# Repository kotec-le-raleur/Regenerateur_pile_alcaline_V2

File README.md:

# Regenerateur_pile_alcaline_V2
Encore un autre projet à la con pour tenter de recharger des piles alcalines

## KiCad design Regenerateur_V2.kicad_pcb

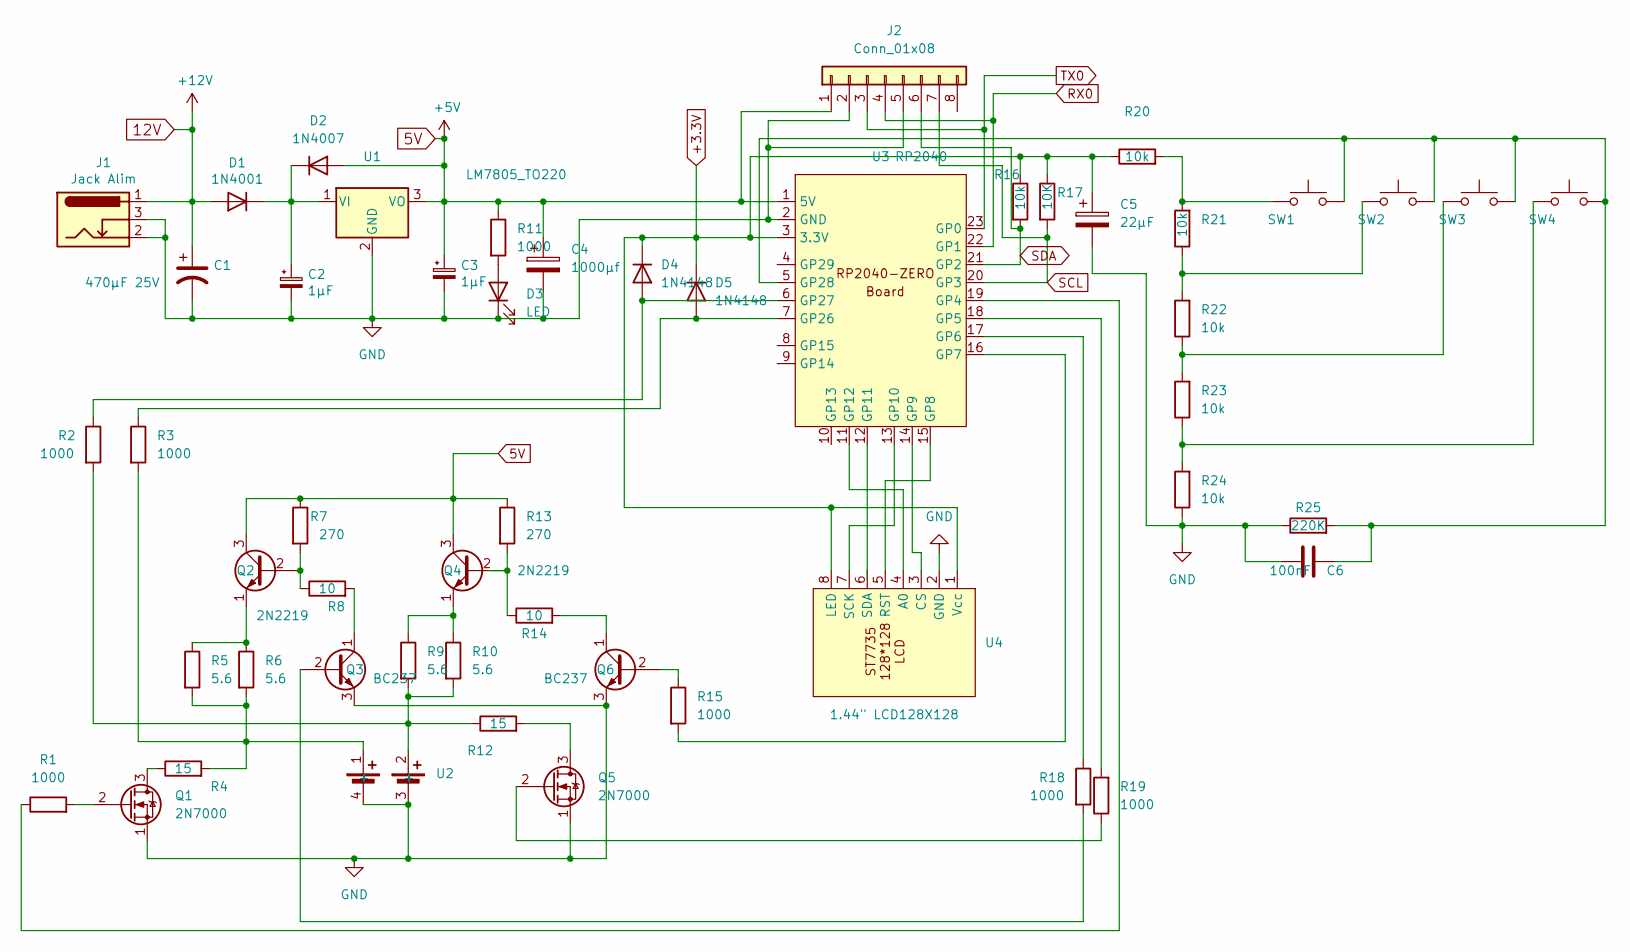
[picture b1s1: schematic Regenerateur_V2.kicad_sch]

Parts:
C1: 470µF 25V; CP_Radial_D10.0mm_P5.00mm
C2, C3: 1µF; C_1206_3216Metric_Pad1.33x1.80mm_HandSolder
C4: 1000µf; CP_Radial_D10.0mm_P7.50mm
C5: 22µF; CP_Radial_D5.0mm_P2.50mm
C6: 100nF; C_Rect_L7.0mm_W2.5mm_P5.00mm
D1: 1N4001; D_DO-41_SOD81_P10.16mm_Horizontal
D2: 1N4007; D_DO-41_SOD81_P10.16mm_Horizontal
D3: LED; LED_D5.0mm
D4, D5: 1N4148; D_A-405_P7.62mm_Horizontal
J1: Jack Alim; BarrelJack_Wuerth_6941xx301002
J2: Conn_01x08; PinHeader_1x08_P2.54mm_Vertical
Q1, Q5: 2N7000; TO-92_HandSolder
Q2, Q4: 2N2219; TO-5-4
Q3, Q6: BC237; TO-92_HandSolder
R1, R2, R3, R11, R15, R18, R19: 1000; R_Axial_DIN0204_L3.6mm_D1.6mm_P7.62mm_Horizontal
R4, R12: 15; R_Axial_DIN0204_L3.6mm_D1.6mm_P7.62mm_Horizontal
R5, R6, R9, R10: 5.6; R_Axial_DIN0204_L3.6mm_D1.6mm_P7.62mm_Horizontal
R7, R13: 270; R_Axial_DIN0204_L3.6mm_D1.6mm_P7.62mm_Horizontal
R8, R14: 10; R_Axial_DIN0204_L3.6mm_D1.6mm_P7.62mm_Horizontal
R16, R20, R21, R22, R23, R24: 10k; R_Axial_DIN0204_L3.6mm_D1.6mm_P7.62mm_Horizontal
R17: 10K; R_Axial_DIN0204_L3.6mm_D1.6mm_P7.62mm_Horizontal
R25: 220K; R_Axial_DIN0204_L3.6mm_D1.6mm_P7.62mm_Horizontal
SW1, SW2, SW3, SW4: SW_Push; SW_PUSH_6mm_H13mm
U1: LM7805_TO220; TO-220-3_Vertical
U2: AAX2_Case
U3: RP2040; RP2040_zero_mini
U4: 1.44" LCD128X128; LCD128X128

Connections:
5V: C3.1, C4.1, D2.2 (A), J2.1, Q2.3 (C), Q4.3 (C), R7.1, R11.1, R13.1, U1.3 (VO), U3.1 (5V)
12V: C1.1, D1.2 (A), J1.1
+3.3V: C5.1, D4.1 (K), D5.1 (K), R16.1, R17.1, R20.1, U3.3 (3.3V), U4.1 (Vcc), U4.8 (LED)
GND: C1.2, C2.2, C3.2, C4.2, C5.2, C6.1, D3.1 (K), J1.2, J1.3, J2.2, J2.5, Q1.1 (S), Q3.3 (E), Q5.1 (S), Q6.3 (E), R24.1, R25.1, U1.2 (GND), U2.3 (-), U2.4 (-), U3.2 (GND), U4.2 (GND)
unnamed: C2.1, D1.1 (K), D2.1 (K), U1.1 (VI)
unnamed: D3.2 (A), R11.2
unnamed: D4.2 (A), R2.1, U3.6 (GP27)
unnamed: D5.2 (A), R3.1, U3.7 (GP26)
unnamed: Q1.3 (D), R4.1
unnamed: Q1.2 (G), R1.2
unnamed: Q2.2 (B), Q2.4, R7.2, R8.1
unnamed: Q2.1 (E), R5.1, R6.1
unnamed: Q3.2 (B), R18.2
unnamed: Q3.1 (C), R8.2
unnamed: Q4.2 (B), Q4.4, R13.2, R14.1
unnamed: Q4.1 (E), R9.1, R10.1
unnamed: Q5.3 (D), R12.2
unnamed: Q5.2 (G), R19.1
unnamed: Q6.2 (B), R15.1
unnamed: Q6.1 (C), R14.2
unnamed: R3.2, R4.2, R5.2, R6.2, U2.1 (+)
unnamed: R2.2, R9.2, R10.2, R12.1, U2.2 (+)
unnamed: R20.2, R21.2, SW1.1
unnamed: R21.1, R22.2, SW2.1
unnamed: R22.1, R23.2, SW3.1
unnamed: R23.1, R24.2, SW4.1
unnamed: R1.1, U3.19 (GP4)
unnamed: R19.2, U3.18 (GP5)
unnamed: R18.1, U3.17 (GP6)
unnamed: R15.2, U3.16 (GP7)
unnamed: U3.15 (GP8), U4.5 (RST)
unnamed: U3.14 (GP9), U4.3 (CS)
unnamed: U3.13 (GP10), U4.7 (SCK)
unnamed: U3.11 (GP12), U4.4 (A0)
unnamed: C6.2, R25.2, SW1.2, SW2.2, SW3.2, SW4.2, U3.5 (GP28)
RX0: J2.4, U3.22 (GP1)
SCL: J2.7, R17.2, U3.20 (GP3)
SDA: J2.6, R16.2, U3.21 (GP2)
TX0: J2.3, U3.23 (GP0)

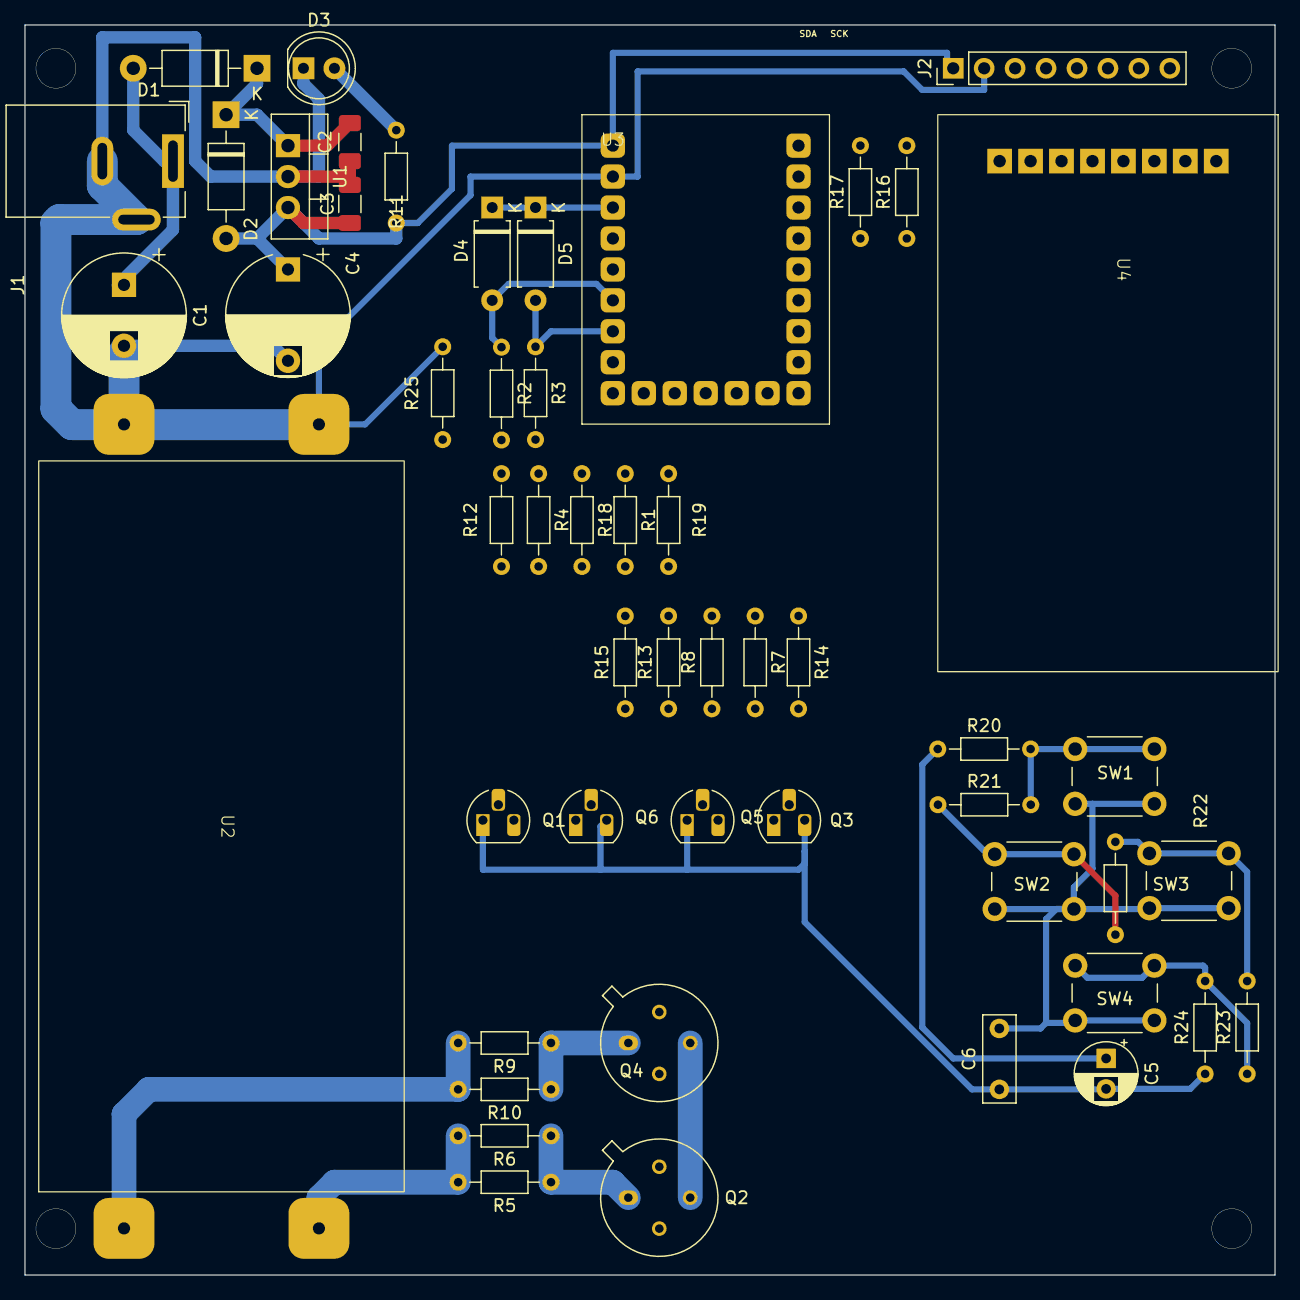
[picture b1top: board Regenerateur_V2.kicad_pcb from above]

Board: 2 copper layers, 102.6 x 102.6 mm, 52 parts (0 on the bottom side), 39 nets.

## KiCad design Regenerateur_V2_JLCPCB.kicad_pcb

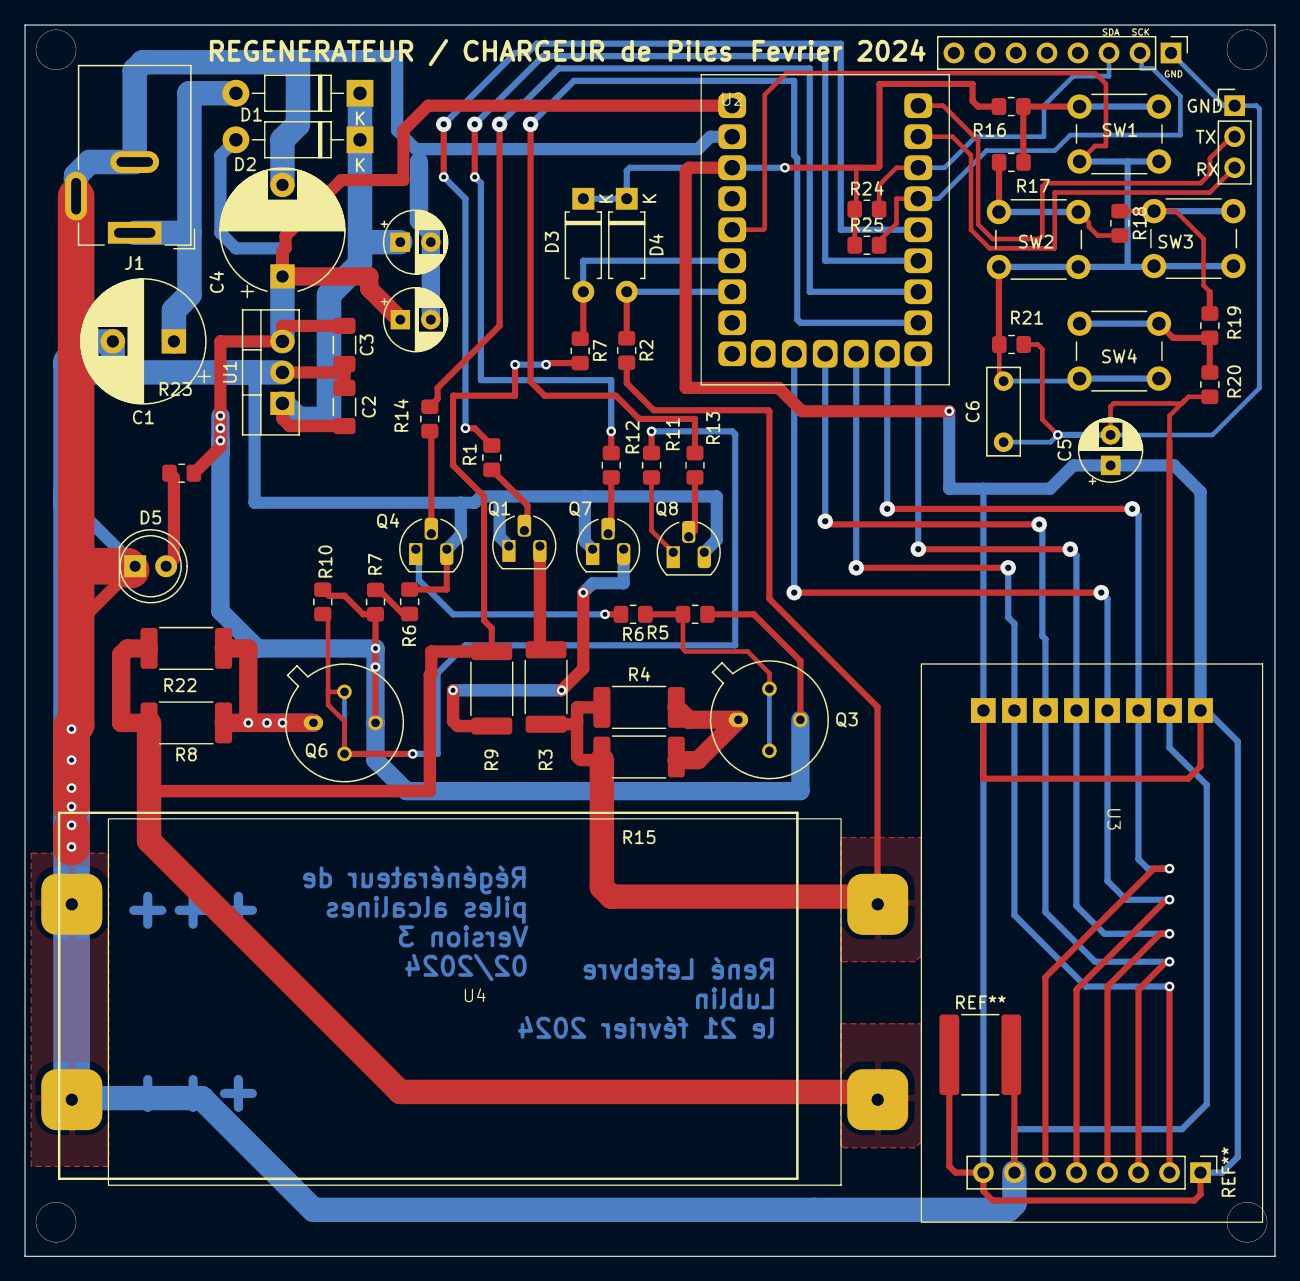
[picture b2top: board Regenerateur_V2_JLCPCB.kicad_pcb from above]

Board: 2 copper layers, 102.4 x 100.8 mm, 53 parts (0 on the bottom side), 39 nets.

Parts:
C1: 470µF 25V; CP_Radial_D10.0mm_P5.00mm
C2, C3: 1µF; C_1206_3216Metric_Pad1.33x1.80mm_HandSolder
C4: 1000µf; CP_Radial_D10.0mm_P7.50mm
C5: 22µF; CP_Radial_D5.0mm_P2.50mm
C6: 100nF; C_Rect_L7.0mm_W2.5mm_P5.00mm
D1: 1N4001; D_DO-41_SOD81_P10.16mm_Horizontal
D2: 1N4007; D_DO-41_SOD81_P10.16mm_Horizontal
D3, D4: 1N4148; D_A-405_P7.62mm_Horizontal
D5: LED; LED_D5.0mm
J1: Jack Alim; BarrelJack_Wuerth_6941xx301002
Q1, Q7: 2N7000; TO-92_HandSolder
Q3, Q6: 2N2219; TO-5-4
Q4, Q8: BC237; TO-92_HandSolder
R1, R2, R7#2, R12, R13, R14, R23: 1000; R_0805_2012Metric_Pad1.20x1.40mm_HandSolder
R3, R9: 15; R_2512_6332Metric_Pad1.40x3.35mm_HandSolder
R4, R8, R15, R22: 5.6; R_2512_6332Metric_Pad1.40x3.35mm_HandSolder
R5, R10: 270; R_0805_2012Metric_Pad1.20x1.40mm_HandSolder
R6, R11: 10; R_0805_2012Metric_Pad1.20x1.40mm_HandSolder
R6#2: 240; R_0805_2012Metric_Pad1.20x1.40mm_HandSolder
R7: 820; R_0805_2012Metric_Pad1.20x1.40mm_HandSolder
R16, R17, R18, R19, R20, R24: 10k; R_0805_2012Metric_Pad1.20x1.40mm_HandSolder
R21: 220K; R_0805_2012Metric_Pad1.20x1.40mm_HandSolder
R25: 10K; R_0805_2012Metric_Pad1.20x1.40mm_HandSolder
SW1, SW2, SW3, SW4: SW_Push; SW_PUSH_6mm_H13mm
U1: LM7805_TO220; TO-220-3_Vertical
U2: RP2040; RP2040_zero_mini
U3: 1.44" LCD128X128; LCD128X128
U4: AAX2_Case

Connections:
5V: C3.1, C4.1, D2.2 (A), Q3.3 (C), Q6.3 (C), R5.1, R7.1, R10.1, R23.1, U1.3 (VO), U2.1 (5V)
12V: C1.1, D1.2 (A), J1.1
+3.3V: C5.1, D3.1 (K), D4.1 (K), R16.1, R24.1, R25.1, U2.3 (3.3V), U3.1 (Vcc), U3.8 (LED)
GND: C1.2, C2.2, C3.2, C4.2, C5.2, C6.1, D5.1 (K), J1.2, J1.3, Q1.1 (S), Q4.3 (E), Q7.1 (S), Q8.3 (E), R6#2.2, R20.1, R21.1, U1.2 (GND), U2.2 (GND), U3.2 (GND), U4.3 (-), U4.4 (-)
unnamed: C2.1, D1.1 (K), D2.1 (K), U1.1 (VI)
unnamed: D3.2 (A), R7#2.1, U2.6 (GP27)
unnamed: D4.2 (A), R2.1, U2.7 (GP26)
unnamed: D5.2 (A), R23.2
unnamed: Q1.3 (D), R3.1
unnamed: Q1.2 (G), R1.2
unnamed: Q3.2 (B), R5.2, R6.1
unnamed: Q3.1 (E), R4.1, R15.1
unnamed: Q4.2 (B), R14.2
unnamed: Q4.1 (C), R6.2
unnamed: Q6.2 (B), R10.2, R11.1
unnamed: Q6.1 (E), R8.1, R22.1
unnamed: Q7.3 (D), R9.2
unnamed: Q7.2 (G), R12.1
unnamed: Q8.2 (B), R13.1
unnamed: Q8.1 (C), R11.2
unnamed: R2.2, R3.2, R4.2, R15.2, U4.1 (+)
unnamed: R16.2, R17.2, SW1.1
unnamed: R17.1, R18.2, SW2.1
unnamed: R18.1, R19.2, SW3.1
unnamed: R19.1, R20.2, SW4.1
unnamed: R7#2.2, R8.2, R9.1, R22.2, U4.2 (+)
unnamed: R6#2.1, R7.2
unnamed: R1.1, U2.19 (GP4)
unnamed: R12.2, U2.18 (GP5)
unnamed: R14.1, U2.17 (GP6)
unnamed: R13.2, U2.16 (GP7)
unnamed: U2.15 (GP8), U3.5 (RST)
unnamed: U2.14 (GP9), U3.3 (CS)
unnamed: U2.13 (GP10), U3.7 (SCK)
unnamed: U2.12 (GP11), U3.6 (SDA)
unnamed: U2.11 (GP12), U3.4 (A0)
unnamed: C6.2, R21.2, SW1.2, SW2.2, SW3.2, SW4.2, U2.5 (GP28)
SCL: R25.2, U2.20 (GP3)
SDA: R24.2, U2.21 (GP2)

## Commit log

2025-02-12 Create lib
    lib pour micropython
2025-02-12 Add files via upload
    Driver pour l'écran LCD
